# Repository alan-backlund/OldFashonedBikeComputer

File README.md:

# OldFashonedBikeComputer
Bicycle computer like they don't make anymore. Distance &amp; cadence and a battery that lasts years.

## Overview
OldFashonedBikeComputer (OFBC) is a bicycle computer based on the STM32L031 mpu and a Sharp LS013B7DH03 display. It monitors distance travelled, cadence and temperature. It fits in a small (35mm by 55mm) case and will hopefully run for two years on a CR2032 coin cell.

### The State of This Project
I have built a unit and am using it on my bike. IT works "Good enough" for my requirements so I am moving on to other projects for now. A number of options are set the way I like them and can only be changed by re-compiling the firmware.

### To Do
* Larger screen.
* Switch to a processor with more flash (32k is barely enough).
* More configuration items (kilometres/miles, Celsuis/Farenheit, 12hr/24hr).
* New PCB with the mounting holes in the right place. Original pcb has been literally hacked to fit.

## Contributing
If you have a suggestion for an improvement, please fork the repo and create a pull request. You can also simply open an issue or for more general feature requests, head over to the discussions.

## License
Distributed under the GPL v3 License.

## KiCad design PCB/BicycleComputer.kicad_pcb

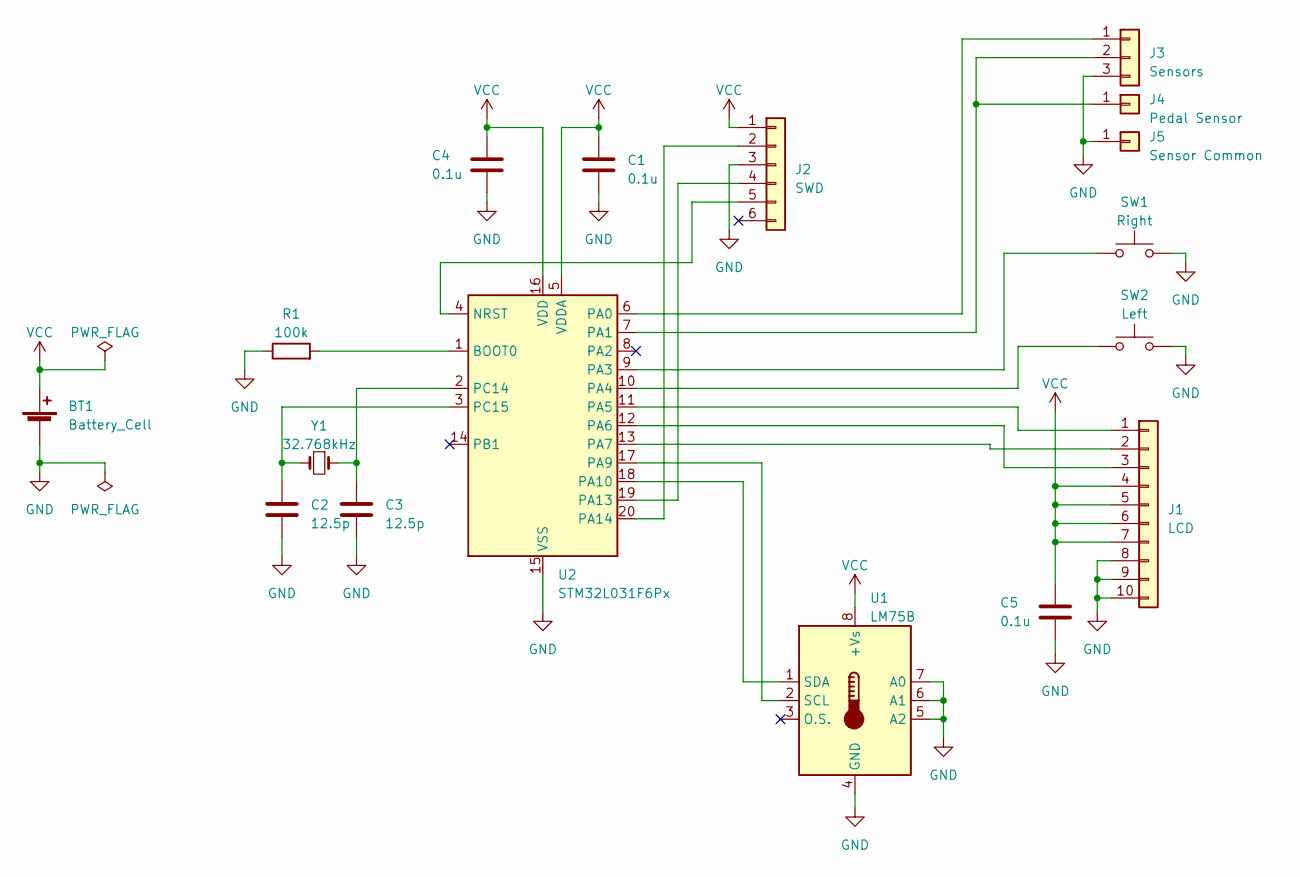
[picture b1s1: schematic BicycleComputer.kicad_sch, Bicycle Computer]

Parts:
BT1: Battery_Cell; BatteryHolder_Keystone_3034_1x20mm
C1, C4, C5: 0.1u; C_0805_2012Metric
C2, C3: 12.5p; C_0805_2012Metric
J1: LCD; Hirose_FH12-10S-0.5SH_1x10-1MP_P0.50mm_Horizontal
J2: SWD; PinHeader_1x06_P2.54mm_Vertical
J3: Sensors; PinHeader_1x03_P2.54mm_Horizontal
J4: Pedal Sensor; PinHeader_1x01_P2.54mm_Vertical
J5: Sensor Common; PinHeader_1x01_P2.54mm_Vertical
R1: 100k; R_0805_2012Metric
SW1: Right; SW_Push_1P1T_NO_6x6mm_H9.5mm
SW2: Left; SW_Push_1P1T_NO_6x6mm_H9.5mm
U1: LM75B; HVSSOP-8-1EP_3x3mm_P0.65mm_EP1.57x1.89mm
U2: STM32L031F6Px; TSSOP-20_4.4x6.5mm_P0.65mm
Y1: 32.768kHz; Crystal_C38-LF_D3.0mm_L8.0mm_Horizontal

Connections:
GND: BT1.2 (-), C1.2, C2.2, C3.2, C4.2, C5.2, J1.8, J1.9, J1.10, J2.3, J3.3, J5.1, R1.1, SW1.2, SW2.2, U1.4 (GND), U1.5 (A2), U1.6 (A1), U1.7 (A0), U2.15 (VSS)
unnamed: J1.1, U2.11 (PA5)
unnamed: J1.2, U2.13 (PA7)
unnamed: J1.3, U2.12 (PA6)
unnamed: J2.2, U2.20 (PA14)
unnamed: J2.4, U2.19 (PA13)
unnamed: J2.5, U2.4 (NRST)
unnamed: J3.1, U2.6 (PA0)
unnamed: J3.2, J4.1, U2.7 (PA1)
unnamed: U1.2 (SCL), U2.17 (PA9)
unnamed: U1.1 (SDA), U2.18 (PA10)
unnamed: R1.2, U2.1 (BOOT0)
unnamed: SW1.1, U2.9 (PA3)
unnamed: SW2.1, U2.10 (PA4)
unnamed: C3.1, U2.2 (PC14), Y1.1
unnamed: C2.1, U2.3 (PC15), Y1.2
VCC: BT1.1 (+), C1.1, C4.1, C5.1, J1.4, J1.5, J1.6, J1.7, J2.1, U1.8 (+Vs), U2.5 (VDDA), U2.16 (VDD)

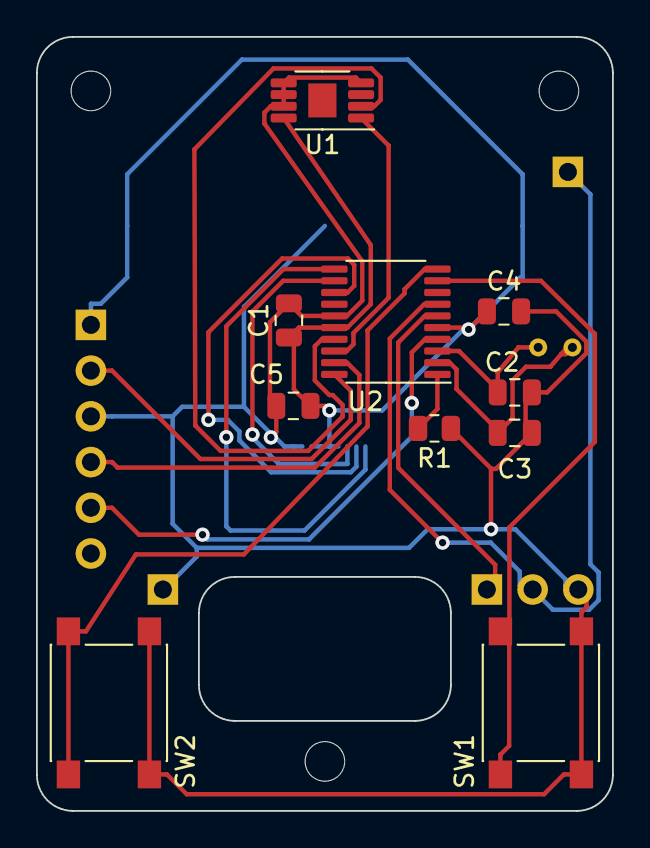
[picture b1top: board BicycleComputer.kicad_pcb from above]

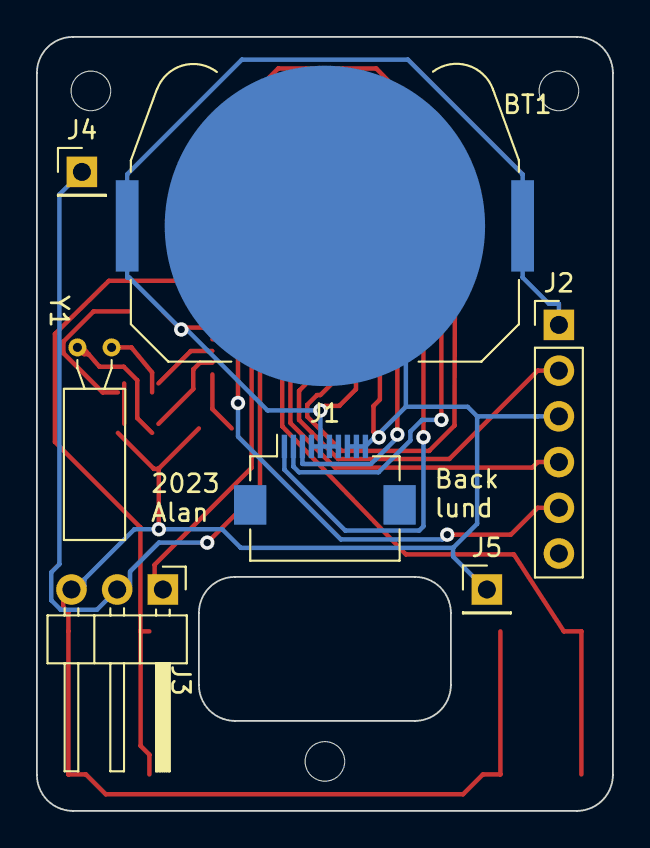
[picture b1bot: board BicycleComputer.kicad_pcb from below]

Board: 2 copper layers, 32.0 x 43.0 mm, 20 parts (7 on the bottom side), 17 nets.

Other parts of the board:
REF00, REF01, REF02: MountingHole_2.2mm_M2

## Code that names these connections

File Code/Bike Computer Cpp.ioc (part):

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Mcu.Name=STM32L031F(4-6)Px
Mcu.Package=TSSOP20
Mcu.UserName=STM32L031F6Px
PA0-CK_IN.GPIOParameters=GPIO_PuPd,GPIO_Label,GPIO_ModeDefaultEXTI
PA0-CK_IN.GPIO_Label=WHEEL
PA0-CK_IN.GPIO_ModeDefaultEXTI=GPIO_MODE_IT_FALLING
PA0-CK_IN.GPIO_PuPd=GPIO_PULLUP
PA0-CK_IN.Signal=GPXTI0
PA1.GPIOParameters=GPIO_PuPd,GPIO_Label,GPIO_ModeDefaultEXTI
PA1.GPIO_Label=PEDAL
PA1.GPIO_ModeDefaultEXTI=GPIO_MODE_IT_FALLING
PA1.GPIO_PuPd=GPIO_PULLUP
PA1.Signal=GPXTI1
PA10.GPIOParameters=GPIO_Pu
PA10.GPIO_Pu=GPIO_PULLUP
PA10.Mode=I2C
PA10.Signal=I2C1_SDA
PA13.Mode=Serial_Wire
PA13.Signal=SYS_SWDIO
PA14.Mode=Serial_Wire
PA14.Signal=SYS_SWCLK
PA2.Signal=GPIO_Analog
PA3.GPIOParameters=GPIO_PuPd,GPIO_Label,GPIO_ModeDefaultEXTI
PA3.GPIO_Label=RIGHT
PA3.GPIO_ModeDefaultEXTI=GPIO_MODE_IT_FALLING
PA3.GPIO_PuPd=GPIO_PULLUP
PA3.Signal=GPXTI3
PA4.GPIOParameters=GPIO_PuPd,GPIO_Label,GPIO_ModeDefaultEXTI
PA4.GPIO_Label=LEFT
PA4.GPIO_ModeDefaultEXTI=GPIO_MODE_IT_FALLING
PA4.GPIO_PuPd=GPIO_PULLUP
PA4.Signal=GPXTI4
PA5.Mode=TX_Only_Simplex_Unidirect_Master
PA5.Signal=SPI1_SCK
PA6.GPIOParameters=GPIO_Label
PA6.GPIO_Label=SPI1_CS
PA6.Signal=GPIO_Output
PA7.Mode=TX_Only_Simplex_Unidirect_Master
PA7.Signal=SPI1_MOSI
PA9.GPIOParameters=GPIO_Pu
PA9.GPIO_Pu=GPIO_PULLUP
PA9.Mode=I2C
PA9.Signal=I2C1_SCL
PB1.Signal=GPIO_Analog
PC14-OSC32_IN.Mode=LSE-External-Oscillator
PC14-OSC32_IN.Signal=RCC_OSC32_IN
PC15-OSC32_OUT.Mode=LSE-External-Oscillator
PC15-OSC32_OUT.Signal=RCC_OSC32_OUT
RCC.HSE_VALUE=8000000
RCC.SYSCLKFreq_VALUE=2097000
board=custom
